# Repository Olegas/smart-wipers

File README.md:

# smart-wipers
Умные дворники: автоматизируем автомобиль
https://habr.com/ru/company/tensor/blog/552726/

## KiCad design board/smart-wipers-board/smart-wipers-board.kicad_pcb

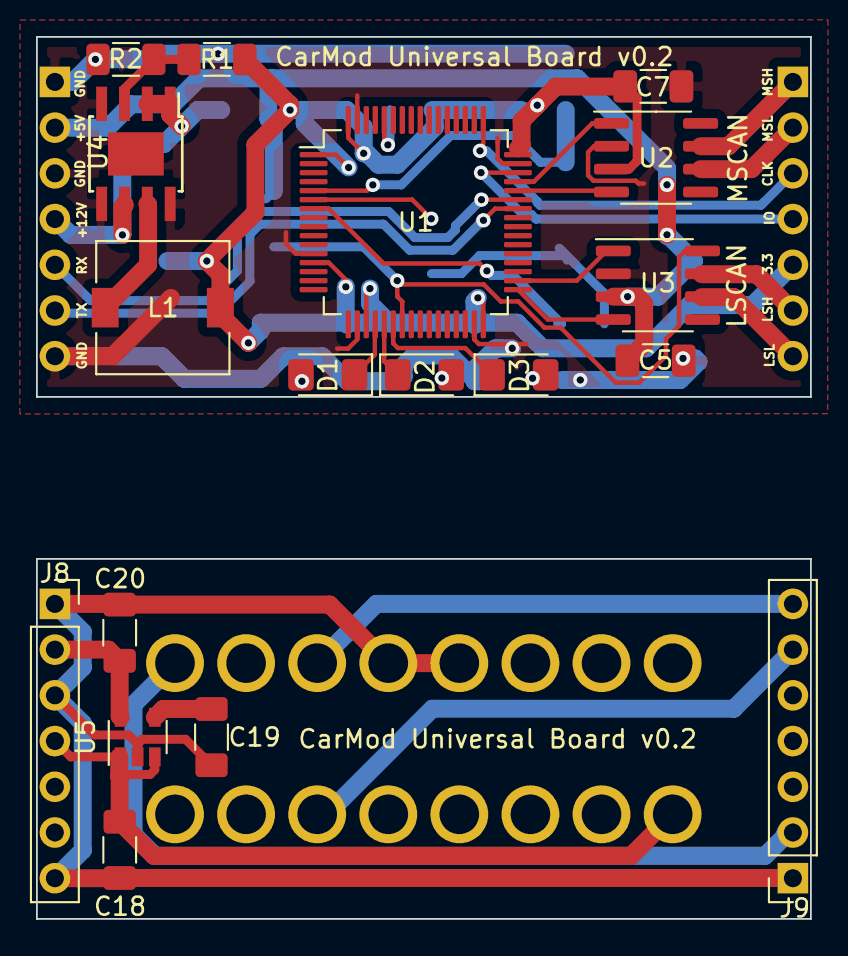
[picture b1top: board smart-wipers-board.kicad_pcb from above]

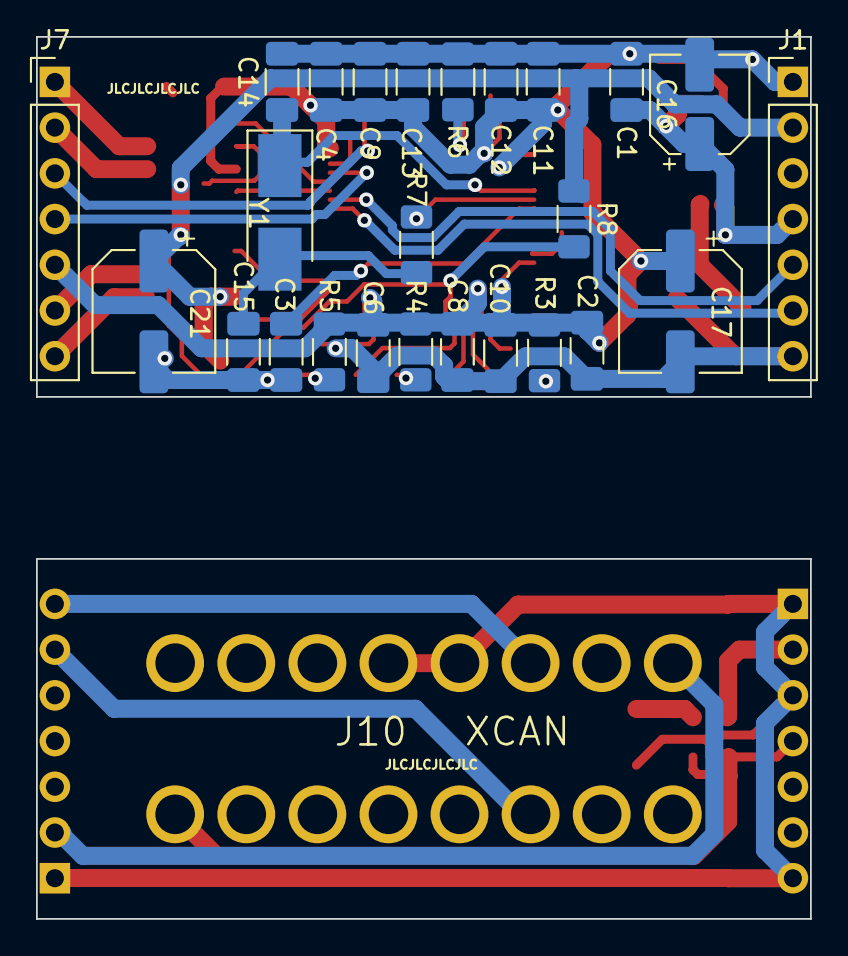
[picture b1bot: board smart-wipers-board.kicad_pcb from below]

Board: 2 copper layers, 43.0 x 49.0 mm, 44 parts (25 on the bottom side), 37 nets.

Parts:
C1, C2, C3, C4, C5, C6, C7, C8, C9, C10, C11: 100nF; C_1206_3216Metric_Pad1.33x1.80mm_HandSolder
C12, C18: 1uF; C_1206_3216Metric_Pad1.33x1.80mm_HandSolder
C13: 10uF; C_1206_3216Metric_Pad1.33x1.80mm_HandSolder
C14, C15: 15pF; C_1206_3216Metric_Pad1.33x1.80mm_HandSolder
C16: 10uF 25V; CP_Elec_5x5.7
C17, C21: 100uF 6.3V; CP_Elec_6.3x5.4
C19: 10nF; C_1206_3216Metric_Pad1.33x1.80mm_HandSolder
C20: 2.2uF; C_1206_3216Metric_Pad1.33x1.80mm_HandSolder
D1: LED_RED; LED_1206_3216Metric_Pad1.42x1.75mm_HandSolder
D2: LED_GREEN; LED_1206_3216Metric_Pad1.42x1.75mm_HandSolder
D3: LED_BLUE; LED_1206_3216Metric_Pad1.42x1.75mm_HandSolder
J1: X1; PinHeader_1x07_P2.54mm_Vertical
J7: X2; PinHeader_1x07_P2.54mm_Vertical
J8: XC1; PinSocket_1x07_P2.54mm_Vertical
J9: XC2; PinSocket_1x07_P2.54mm_Vertical
J10: XCAN; OBDII
L1: CDRH6D38NP-3R3NC; L_7.3x7.3_H3.5
R1: 16K; R_1206_3216Metric_Pad1.30x1.75mm_HandSolder
R2: 5.1K; R_1206_3216Metric_Pad1.30x1.75mm_HandSolder
R3: 56; R_1206_3216Metric_Pad1.30x1.75mm_HandSolder
R4, R5, R8: 15; R_1206_3216Metric_Pad1.30x1.75mm_HandSolder
R6: 10K; R_1206_3216Metric_Pad1.30x1.75mm_HandSolder
R7: 390; R_1206_3216Metric_Pad1.30x1.75mm_HandSolder
U1: STM32F105R8Tx; LQFP-64_10x10mm_P0.5mm
U2: SN65HVD232; SOIC-8_3.9x4.9mm_P1.27mm
U3: MCP2551-I-SN; SOIC-8_3.9x4.9mm_P1.27mm
U4: ST1S10PHR; TI_SO-PowerPAD-8
U5: LP2985-5.0; SOT-23-5
Y1: 8Mhz; Crystal_SMD_5032-2Pin_5.0x3.2mm_HandSoldering

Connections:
+5V: C5.1, C21.1, J1.2, R8.1, U3.3
+12V: C1.1, C16.1, J1.4, U4.1, U4.2, U4.6
/FB: R1.2, R2.1, U4.3
BOOT0: R6.1, U1.60
CAN_5v: C20.1, J8.2, U5.5
CAN_12v: C18.1, J8.4, J10.16, U5.1, U5.3
CAN_GND: C18.2, C19.2, C20.2, J8.1, J8.3, J8.7, J9.1, J10.4, J10.5, U5.2
CAN_LSH: J9.2, J10.1
CAN_MSH: J9.7, J10.3
CAN_MSL: J9.6, J10.11
GNDREF: C1.2, C2.2, C3.2, C4.2, C5.2, C6.2, C7.2, C8.2, C9.2, C10.2, C11.2, C12.2, C13.2, C14.2, C15.2, C16.2, C17.2, C21.2, J1.1, J1.3, J1.7, R2.2, R6.2, U1.12, U1.18, U1.31, U1.47, U1.63, U2.2, U3.2, U4.4, U4.5, U4.8, U4.9
LED_ACC: D2.1, U1.21
LED_BOOT: D1.1, U1.20
LED_LOWT: D3.1, U1.22
LSCANH: J7.6, U3.7
LSCANL: J7.7, U3.6
LSCAN_RX: U1.33, U3.4
LSCAN_TX: U1.34, U3.1
LS_CONTROL: R8.2, U1.23, U3.8
MSCANH: J7.1, U2.7
MSCANL: J7.2, U2.6
MSCAN_RX: U1.44, U2.4
MSCAN_TX: U1.45, U2.1
unnamed: C15.1, R7.2, Y1.2
unnamed: C19.1, U5.4
unnamed: D1.2, R3.2
unnamed: D2.2, R4.2
unnamed: D3.2, R5.2
unnamed: L1.1, U4.7
OSC_IN: C14.1, U1.5, Y1.1
OSC_OUT: R7.1, U1.6
RESET: C3.1, U1.7
SWCLK: J7.3, U1.49
SWDIO: J7.4, U1.46
UART_RX: J1.5, U1.43
UART_TX: J1.6, U1.42
VDD: C2.1, C4.1, C6.1, C7.1, C8.1, C9.1, C10.1, C11.1, C12.1, C13.1, C17.1, J7.5, L1.2, R1.1, R3.1, R4.1, R5.1, U1.1, U1.13, U1.19, U1.32, U1.48, U1.64, U2.3

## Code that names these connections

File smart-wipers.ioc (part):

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Mcu.UserName=STM32F105R8Tx
PA11.Mode=CAN_Activate
PA7.GPIO_ModeDefaultOutputPP=GPIO_MODE_OUTPUT_OD
PA6.GPIO_Label=LED_LOWT
PB13.Signal=CAN2_TX
PA5.PinState=GPIO_PIN_SET
RCC.SYSCLKSource=RCC_SYSCLKSOURCE_HSE
PD1-OSC_OUT.Signal=RCC_OSC_OUT
PA12.Signal=CAN1_TX
PA7.PinState=GPIO_PIN_RESET
PA14.Mode=Serial_Wire
Mcu.Package=LQFP64
PA6.Signal=GPIO_Output
PB12.Mode=CAN_Activate
PA10.Signal=USART1_RX
PA5.GPIOParameters=PinState,GPIO_Label,GPIO_ModeDefaultOutputPP
PA4.GPIO_ModeDefaultOutputPP=GPIO_MODE_OUTPUT_OD
PA6.GPIO_ModeDefaultOutputPP=GPIO_MODE_OUTPUT_OD
PB13.Mode=CAN_Activate
PA4.GPIO_Label=LED_BOOT
PA6.GPIOParameters=PinState,GPIO_Label,GPIO_ModeDefaultOutputPP
PD1-OSC_OUT.Mode=HSE-External-Oscillator
PA10.Mode=Asynchronous
PA6.PinState=GPIO_PIN_SET
PD0-OSC_IN.Signal=RCC_OSC_IN
PA13.Signal=SYS_JTMS-SWDIO
PA9.Mode=Asynchronous
PA4.PinState=GPIO_PIN_SET
PA9.Signal=USART1_TX
PD0-OSC_IN.Mode=HSE-External-Oscillator
PA5.Signal=GPIO_Output
board=custom
PA5.GPIO_ModeDefaultOutputPP=GPIO_MODE_OUTPUT_OD
PA4.GPIOParameters=PinState,GPIO_Label,GPIO_ModeDefaultOutputPP
PA13.Mode=Serial_Wire
Mcu.Name=STM32F105R(8-B-C)Tx
PA4.Signal=GPIO_Output
RCC.SYSCLKFreq_VALUE=8000000
PA7.GPIO_Label=SLOPE_CTL
PA12.Mode=CAN_Activate
PA5.GPIO_Label=LED_ACC
PA11.Signal=CAN1_RX
PA14.Signal=SYS_JTCK-SWCLK
PA7.GPIOParameters=PinState,GPIO_Label,GPIO_ModeDefaultOutputPP
PB12.Signal=CAN2_RX
PA7.Signal=GPIO_Output

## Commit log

2021-01-21 Board v1
2021-02-14 WIP Компилируется
2021-02-14 WIP Разнес периферию по файлам
2021-02-14 WIP Переименовал проект
2021-02-23 WIP Board design
2021-02-23 WIP vehicle state as separate module
2021-02-27 CAN buses swapped because of wrong design of v0.1 board CAN speed configuration adjusted
2021-02-28 WIP checkin wipers was used, beeping when running wipers
2021-03-07 WIP Board v0.2 design
2021-04-09 Code for v0.2 layout
2021-04-09 Board fixes
2021-04-10 Правильная конфигурация шины, срабатываем при 20 градусах для демонстрации
2021-04-10 Одно махание дворниками не триггерит парковку
2021-11-18 Понизил частоту чипа до 8Mhz, убрал TIM1 - не использовался
